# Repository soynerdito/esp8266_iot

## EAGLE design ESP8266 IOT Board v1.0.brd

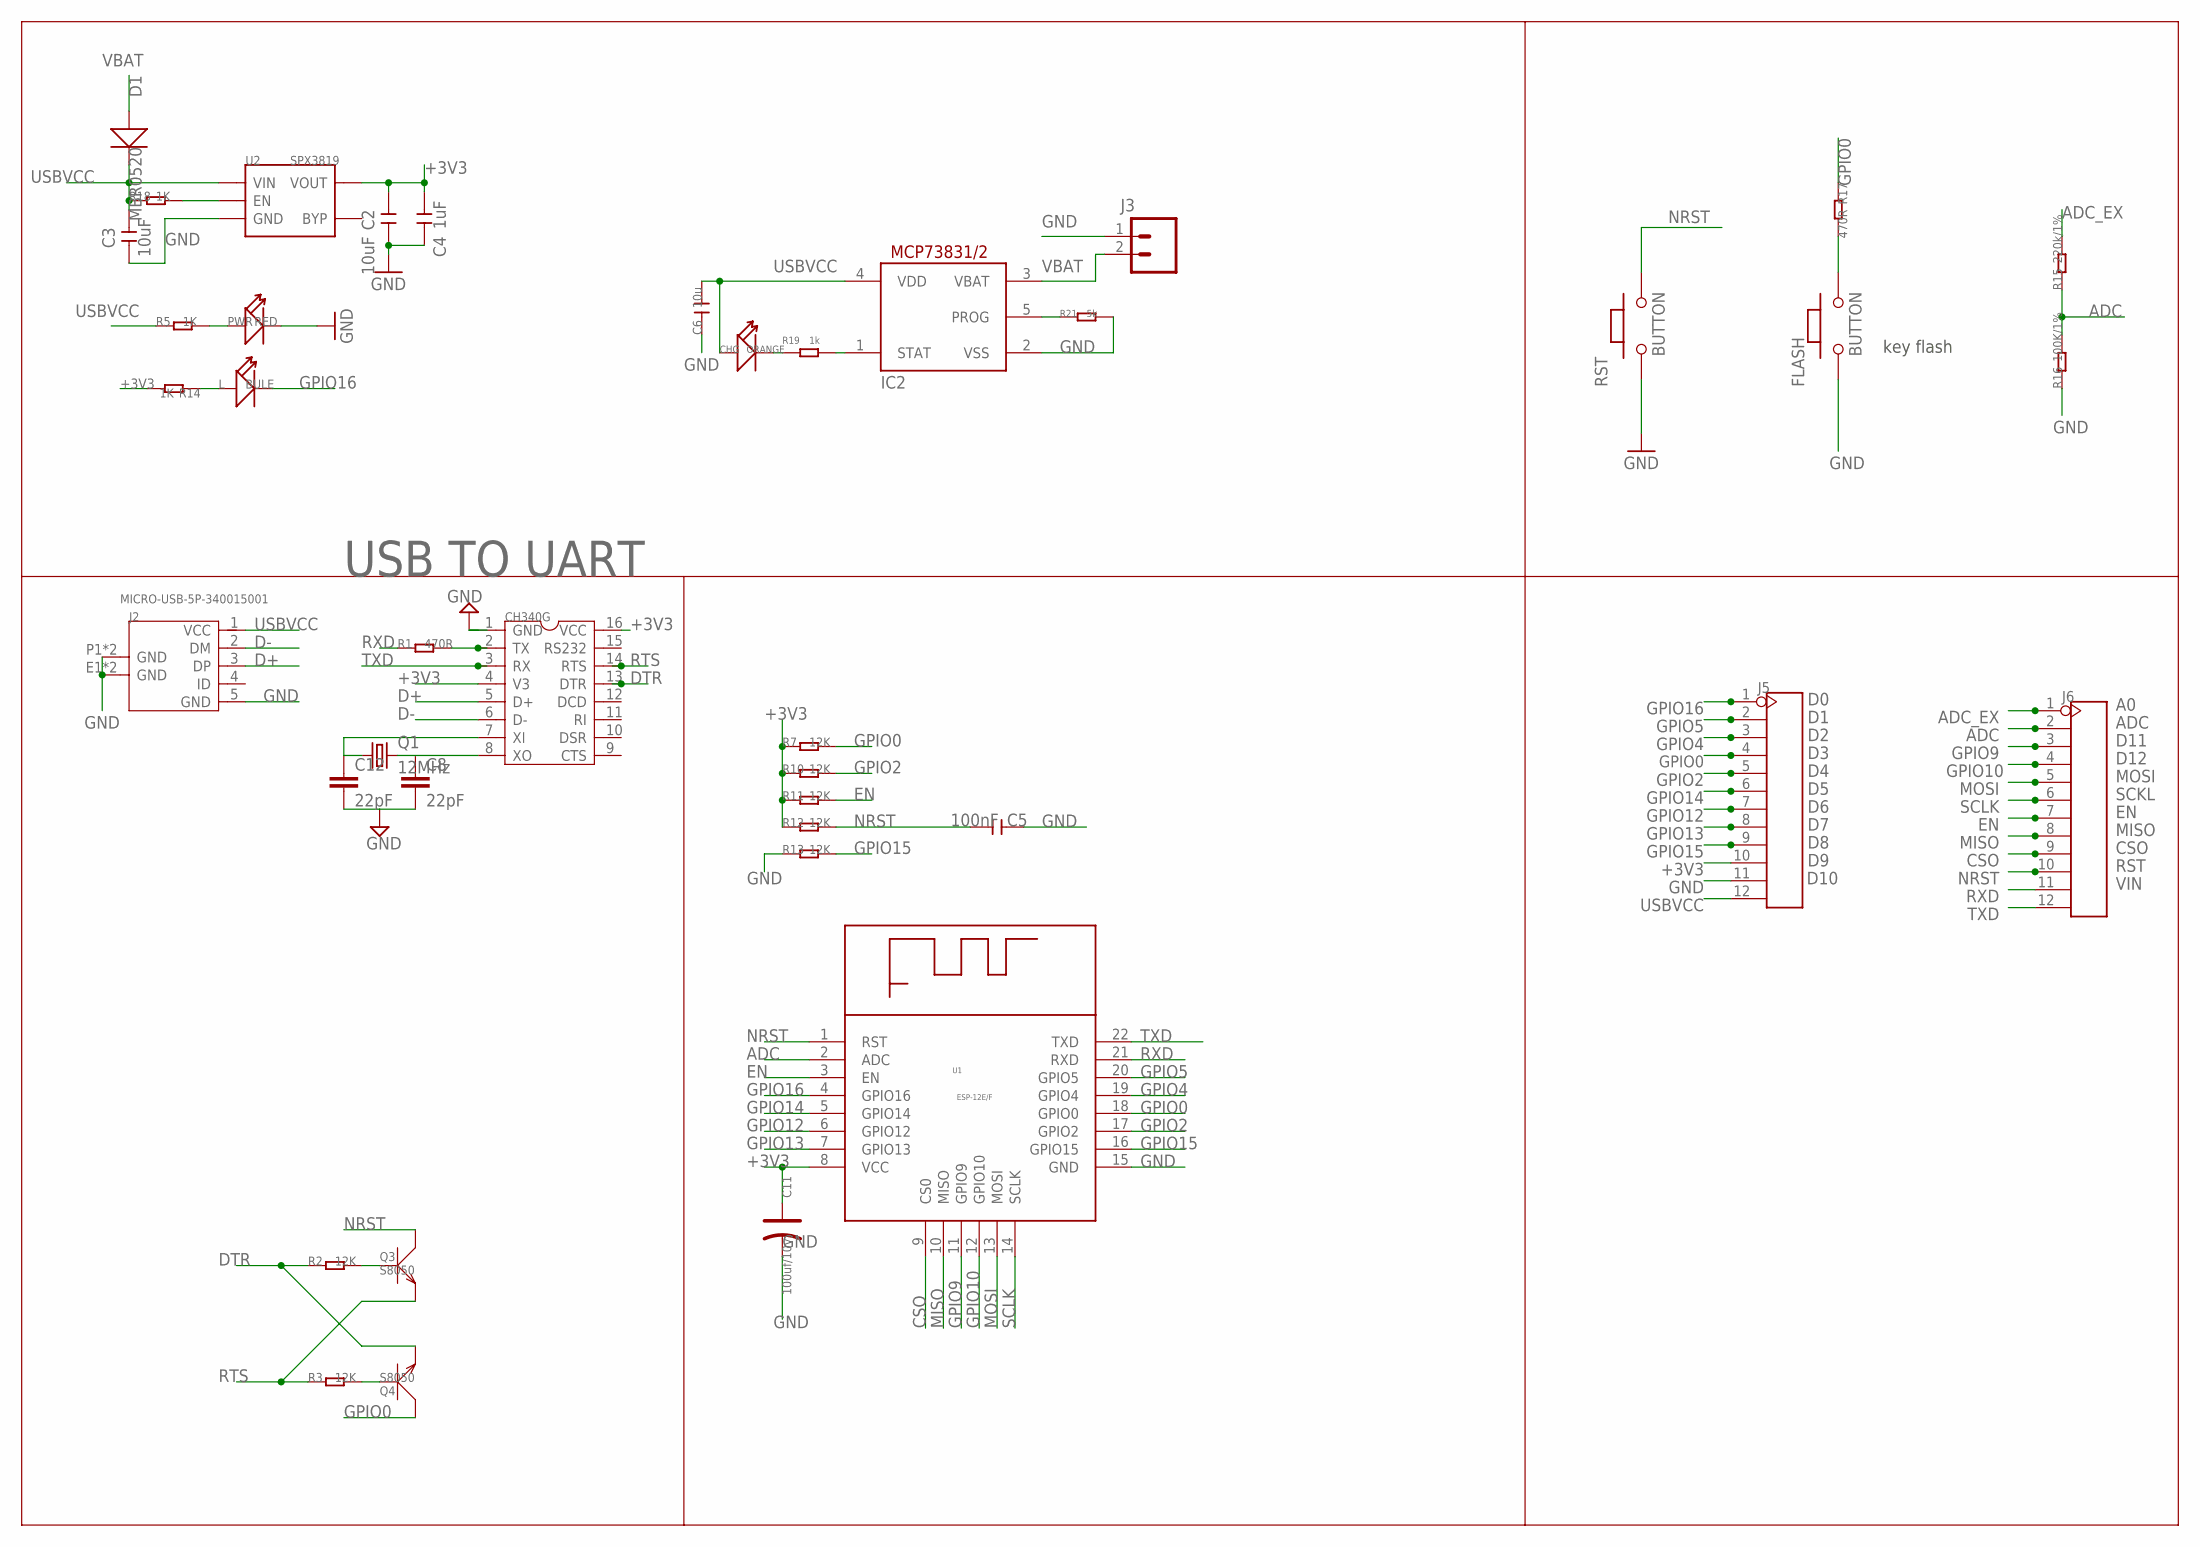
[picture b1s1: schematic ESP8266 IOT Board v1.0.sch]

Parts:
C2, C3: 10uF; C0603
C4: 1uF; C0603
C5: 100nF; C0603
C6: 10u; C0603
C8, C12: 22pF; 0603-CAP
C11: 100uf/10v; AVX-B
CH340G: CH340GCH340G; SOP-16
CHG: ORANGE; D0603
D1: MBR0520; SOD123
FLASH: BUTTON; 157SW
IC2: MCP73831/OT; SOT23-5L
J2: MICRO-USB-5P-340015001; B-SMD-5P
J3: M02-JST-2MM-SMT; JST-2-SMD
J5, J6: HEADER-12P-2.54; 12P-2.54
L: BULE; LED-0603
PWR: RED; LED-0603
Q1: 12MHz; HC49U70
Q3, Q4: S8050; SOT23
R1, R17: 470R; R0603
R2, R3, R7, R10, R11, R12, R13: 12K; R0603
R5, R14, R18: 1K; R0603
R15: 220k/1%; R0603
R16: 100K/1%; R0603
R19: 1k; R0603
R21: 5k; R0603
RST: BUTTON; 157SW
U1: ESP-12E/F
U2: SPX3819; SOT23-5

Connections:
+3V3: C2.2, C4.2, C11.+, CH340G.4 (V3), CH340G.16 (VCC), J5.10, R7.1, R10.1, R11.1, R12.1, R14.2, U1.8 (VCC), U2.5 (VOUT)
ADC: J6.2, R15.1, R16.2, U1.2 (ADC)
ADC_EX: J6.1, R15.2
CSO: J6.9, U1.9 (CS0)
D+: CH340G.5 (D+), J2.3 (DP)
D-: CH340G.6 (D-), J2.2 (DM)
DTR: CH340G.13 (DTR), Q4.2 (E), R2.1
EN: J6.7, R11.2, U1.3 (EN)
GND: C2.1, C3.1, C4.1, C5.1, C6.1, C8.2, C11.-, C12.2, CH340G.1 (GND), FLASH.1, IC2.2 (VSS), J2.5 (GND), J2.E1 (GND), J2.E2 (GND), J2.P1 (GND), J2.P2 (GND), J3.1, J5.11, PWR.-, R13.1, R16.1, R21.2, RST.1, U1.15 (GND), U2.2 (GND)
GPIO0: J5.4, Q4.3 (C), R7.2, R17.1, U1.18 (GPIO0)
GPIO2: J5.5, R10.2, U1.17 (GPIO2)
GPIO4: J5.3, U1.19 (GPIO4)
GPIO5: J5.2, U1.20 (GPIO5)
GPIO9: J6.3, U1.11 (GPIO9)
GPIO10: J6.4, U1.12 (GPIO10)
GPIO12: J5.7, U1.6 (GPIO12)
GPIO13: J5.8, U1.7 (GPIO13)
GPIO14: J5.6, U1.5 (GPIO14)
GPIO15: J5.9, R13.2, U1.16 (GPIO15)
GPIO16: J5.1, L.-, U1.4 (GPIO16)
MISO: J6.8, U1.10 (MISO)
MOSI: J6.5, U1.13 (MOSI)
unnamed: CHG.-, R19.1
unnamed: L.+, R14.1
unnamed: PWR.+, R5.2
unnamed: CH340G.2 (TX), R1.2
unnamed: R18.2, U2.3 (EN)
unnamed: FLASH.2, R17.2
unnamed: Q3.1 (B), R2.2
unnamed: Q4.1 (B), R3.2
unnamed: IC2.1 (STAT), R19.2
unnamed: IC2.5 (PROG), R21.1
NRST: C5.2, J6.10, Q3.3 (C), R12.2, RST.2, U1.1 (RST)
RTS: CH340G.14 (RTS), Q3.2 (E), R3.1
RXD: J6.11, R1.1, U1.21 (RXD)
SCLK: J6.6, U1.14 (SCLK)
TXD: CH340G.3 (RX), J6.12, U1.22 (TXD)
USBVCC: C3.2, C6.2, CHG.+, D1.-, IC2.4 (VDD), J2.1 (VCC), J5.12, R5.1, R18.1, U2.1 (VIN)
VBAT: D1.+, IC2.3 (VBAT), J3.2
XI: C12.1, CH340G.7 (XI), Q1.1
XO: C8.1, CH340G.8 (XO), Q1.2

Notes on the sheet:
key flash
D10
D11
ADC
CSO
MISO
MOSI
SCKL
D12
RST
VIN
USB TO UART

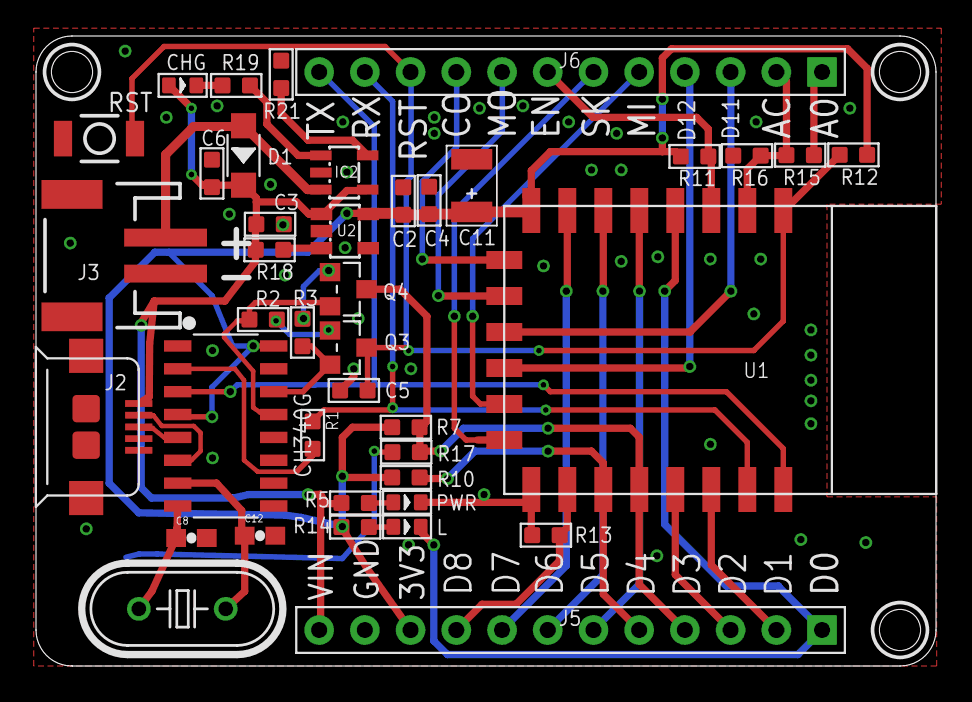
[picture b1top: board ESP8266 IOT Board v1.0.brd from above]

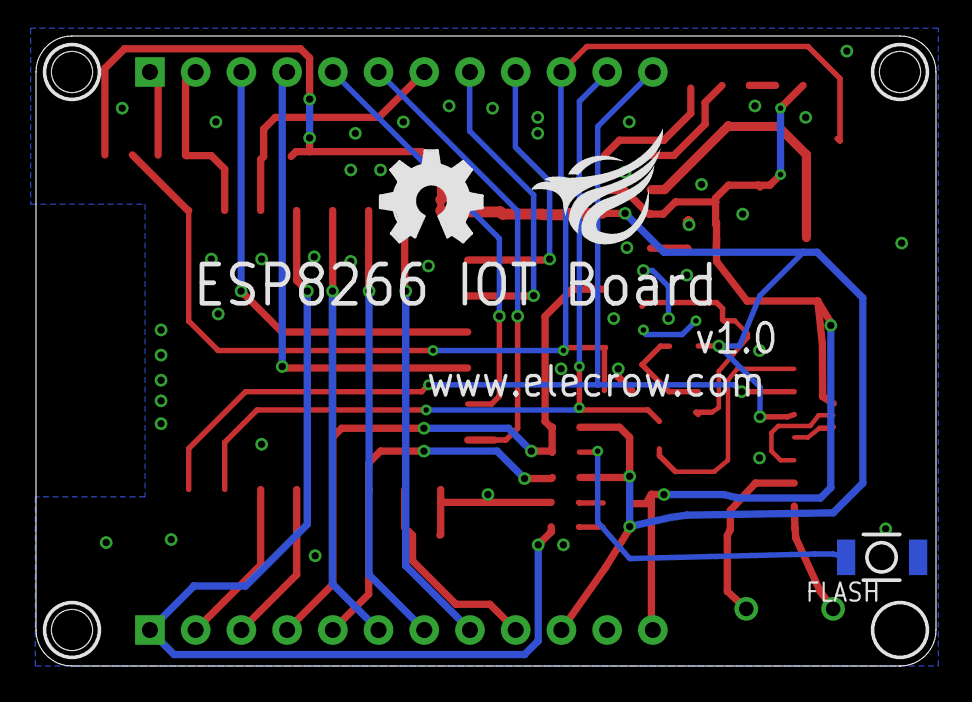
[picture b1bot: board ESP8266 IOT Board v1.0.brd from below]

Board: 2 copper layers, 50.0 x 35.0 mm, 43 parts (3 on the bottom side), 41 nets.

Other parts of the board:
U$2: OSHW_FILLX200_NOTEXT
U$4: ELECROW_NRW_6

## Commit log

2017-03-07 Initital commit

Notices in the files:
parts and their libraries:
SparkFun-Capacitors: Licensing: Creative Commons ShareAlike 4.0 International - https://creativecommons.org/licenses/by-sa/4.0
